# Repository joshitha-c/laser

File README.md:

# ESP32-C3 Laser Tripwire alarm

An intelligent, multi-layered laser security perimeter system built on the ESP32-C3 microcontroller. Features optical tripwire detection, case tamper sensing, motion tracking, real-time clock timestamps, and an OLED status display interface.

---

## Features

* **Triple-Layer Intrusion Detection:**
  * **Laser Tripwire:** Hardware-interrupt beam monitoring via photodiode and LM393 comparator.
  * **Case Tamper:** Microswitch detection if the enclosure lid is opened.
  * **Motion / Shake Guard:** 3-axis LIS3DH accelerometer monitoring for unit displacement or physical sabotage.
* **Visual & Audible Alerts:** 
  * SSD1306 128x64 OLED display showing live state, system time (DS1307 RTC), battery percentage, and specific trip causes.
  * Transistor-driven 3.3V active buzzer siren.
* **Simulation Ready:** Pre-configured for seamless compilation in PlatformIO and testing in the Wokwi simulator.

---

## Hardware Pinout Mapping

| ESP32-C3 Pin | Component / Connection | Type / Logic |
| :--- | :--- | :--- |
| **`GPIO0`** | Photodiode Level | Analog Input |
| **`GPIO1`** | LM393 Laser Trip Signal | Digital Input (Active LOW) |
| **`GPIO2`** | I2C Data (`SDA`) | OLED Display, DS1307 RTC, LIS3DH |
| **`GPIO3`** | I2C Clock (`SCL`) | OLED Display, DS1307 RTC, LIS3DH |
| **`GPIO4`** | Siren Buzzer Driver (`Q1`) | Digital Output (PWM/Pulse) |
| **`GPIO5`** | Arm / Disarm Pushbutton | Digital Input (Active HIGH) |
| **`GPIO6`** | LIS3DH Motion Interrupt (`INT1`) | Digital Input |
| **`GPIO7`** | Battery Sense (100kΩ / 100kΩ Divider) | Analog Input |
| **`GPIO10`**| Case Tamper Microswitch | Digital Input (Active HIGH) |

---
## How to Open and Use the ZIP Project in VS Code

Follow these steps to extract, open, and run the project inside Visual Studio Code using PlatformIO and the Wokwi Simulator.
The zip file:it is in repo releases.
### 1. Unzip the Project Folder
1. Locate the downloaded `.zip` file on your computer.
2. Right-click the `.zip` file and select **Extract All...** (Windows) or double-click it (macOS).
3. Choose a destination directory (e.g., your Desktop or Projects folder) and finish the extraction.

---

### 2. Install Required Extensions in VS Code
If you haven't set up Visual Studio Code for ESP32 development yet, install the required tools:

1. Open **Visual Studio Code**.
2. Click on the **Extensions** icon on the left sidebar (or press `Ctrl + Shift + X`).
3. Search for and install the following two extensions:
   * **[PlatformIO IDE](https://marketplace.visualstudio.com/items?itemName=platformio.platformio-ide)** (Handles building and compiling C++ code for ESP32)
   * **[Wokwi Simulator](https://marketplace.visualstudio.com/items?itemName=Wokwi.wokwi-vscode)** (Simulates the ESP32 hardware and screen)

---

### 3. Open the Extracted Project
1. In VS Code, go to **File** $\rightarrow$ **Open Folder...** (or press `Ctrl + K, Ctrl + O`).
2. Navigate to the folder you extracted in **Step 1**.
3. Select the root folder (the folder containing `platformio.ini` and `wokwi.toml`) and click **Select Folder**.
4. If prompted with *"Do you trust the authors of the files in this folder?"*, click **Yes, I trust the authors**.

---

### 4. Build and Run the Project

#### Option A: Running in Wokwi Simulator (Virtual Hardware)
1. Open the **`diagram.json`** file from the left Explorer pane.
2. Press `Ctrl + Shift + P` (or `Cmd + Shift + P` on Mac) to open the VS Code Command Palette.
3. Type **`Wokwi: Start Simulator`** and press **Enter**.
4. The simulation window will open directly in VS Code, displaying the ILI9341 screen and animated buttons.

# Buzzer audio in vs Code:
* The buzzer noise when running the Wokwi simulator inside the VS Code . The vscode mutes the sounfd from the wokwi simulator so you can't hear it. 
* If you want to listen to the sound effects and music, open the diagram.json file online directly at **[Wokwi.com](https://wokwi.com)**.

---

#  Battery Level Simulation (Potentiometer Knob):
*  In the simulator, the battery level is simulated using a potentiometer (rotary knob).
* How to test battery levels: While the simulation is running, click and drag the knob clockwise on the potentiometer in the simulator window to increase or decrease the voltage.
## schematics:

## pcb:

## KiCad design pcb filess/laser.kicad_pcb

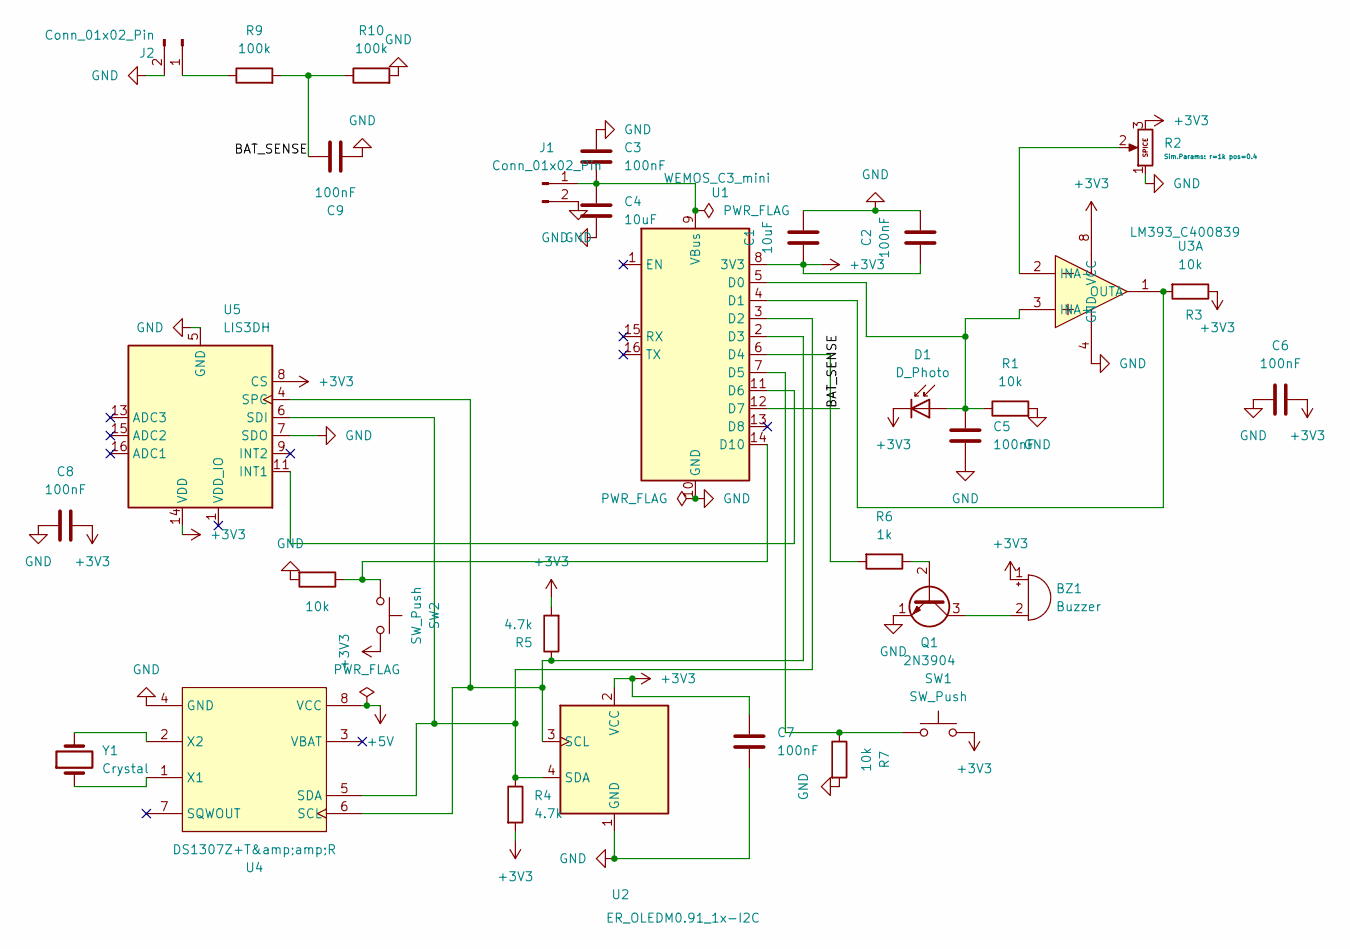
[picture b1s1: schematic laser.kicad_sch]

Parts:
BZ1: Buzzer; Buzzer_12x9.5RM7.6
C1, C4: 10uF; C_0805_2012Metric
C2, C3, C5, C6, C7, C8, C9: 100nF; C_0805_2012Metric
D1: D_Photo; LED_1206_3216Metric
J1: Conn_01x02_Pin; PinHeader_1x02_P2.54mm_Vertical
J2: Conn_01x02_Pin; JST_PH_B2B-PH-K_1x02_P2.00mm_Vertical
Q1: 2N3904; TO-92_Inline
R1, R3, R7, R8: 10k; R_0805_2012Metric
R2: Potentiometer; Potentiometer_Bourns_3296W_Vertical
R4, R5: 4.7k; R_0805_2012Metric
R6: 1k; R_0805_2012Metric
R9, R10: 100k; R_0805_2012Metric
SW1, SW2: SW_Push; SW_SPST_TL3342
U1: WEMOS_C3_mini
U2: ER_OLEDM0.91_1x-I2C
U3: LM393_C400839; SOP-8_L4.9-W3.9-P1.27-LS6.0-BL; MPN LM393; LCSC Part C400839
U4: DS1307Z+T&amp;amp;R; SOIC-8_L5.0-W4.0-P1.27-LS6.0-BL; MPN DS1307Z+T&R; LCSC Part C9868
U5: LIS3DH; LGA-16_3x3mm_P0.5mm_LayoutBorder3x5y
Y1: Crystal; Crystal_AT310_D3.0mm_L10.0mm_Horizontal

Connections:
+3V3: BZ1.1 (+), C1.1, C2.1, C6.2, C7.2, C8.2, D1.1 (K), R2.3, R3.1, R4.2, R5.2, SW1.2, SW2.2, U1.8 (3V3), U2.2 (VCC), U3.8 (VCC), U5.8 (CS), U5.14 (VDD)
+5V: U4.8 (VCC)
/BAT_SENSE: C9.2, R9.2, R10.1, U1.12 (D7)
GND: C1.2, C2.2, C3.1, C4.2, C5.2, C6.1, C7.1, C8.1, C9.1, J1.2, J2.2, Q1.1 (E), R1.2, R2.1, R7.2, R8.2, R10.2, U1.10 (GND), U2.1 (GND), U3.4 (GND), U4.4 (GND), U5.5 (GND), U5.7 (SDO), U5.10 (GND), U5.12 (GND)
unnamed: BZ1.2 (-), Q1.3 (C)
unnamed: C5.1, D1.2 (A), R1.1, U1.5 (D0), U3.3 (INA+)
unnamed: C3.2, C4.1, J1.1, U1.9 (VBus)
unnamed: J2.1, R9.1
unnamed: Q1.2 (B), R6.1
unnamed: R3.2, U1.4 (D1), U3.1 (OUTA)
unnamed: R4.1, U1.3 (D2), U2.4 (SDA), U4.5 (SDA), U5.6 (SDI)
unnamed: R5.1, U1.2 (D3), U2.3 (SCL), U4.6 (SCL), U5.4 (SPC)
unnamed: R6.2, U1.6 (D4)
unnamed: R7.1, SW1.1, U1.7 (D5)
unnamed: U1.11 (D6), U5.11 (INT1)
unnamed: R8.1, SW2.1, U1.14 (D10)
unnamed: R2.2, U3.2 (INA-)
unnamed: U4.1 (X1), Y1.1
unnamed: U4.2 (X2), Y1.2

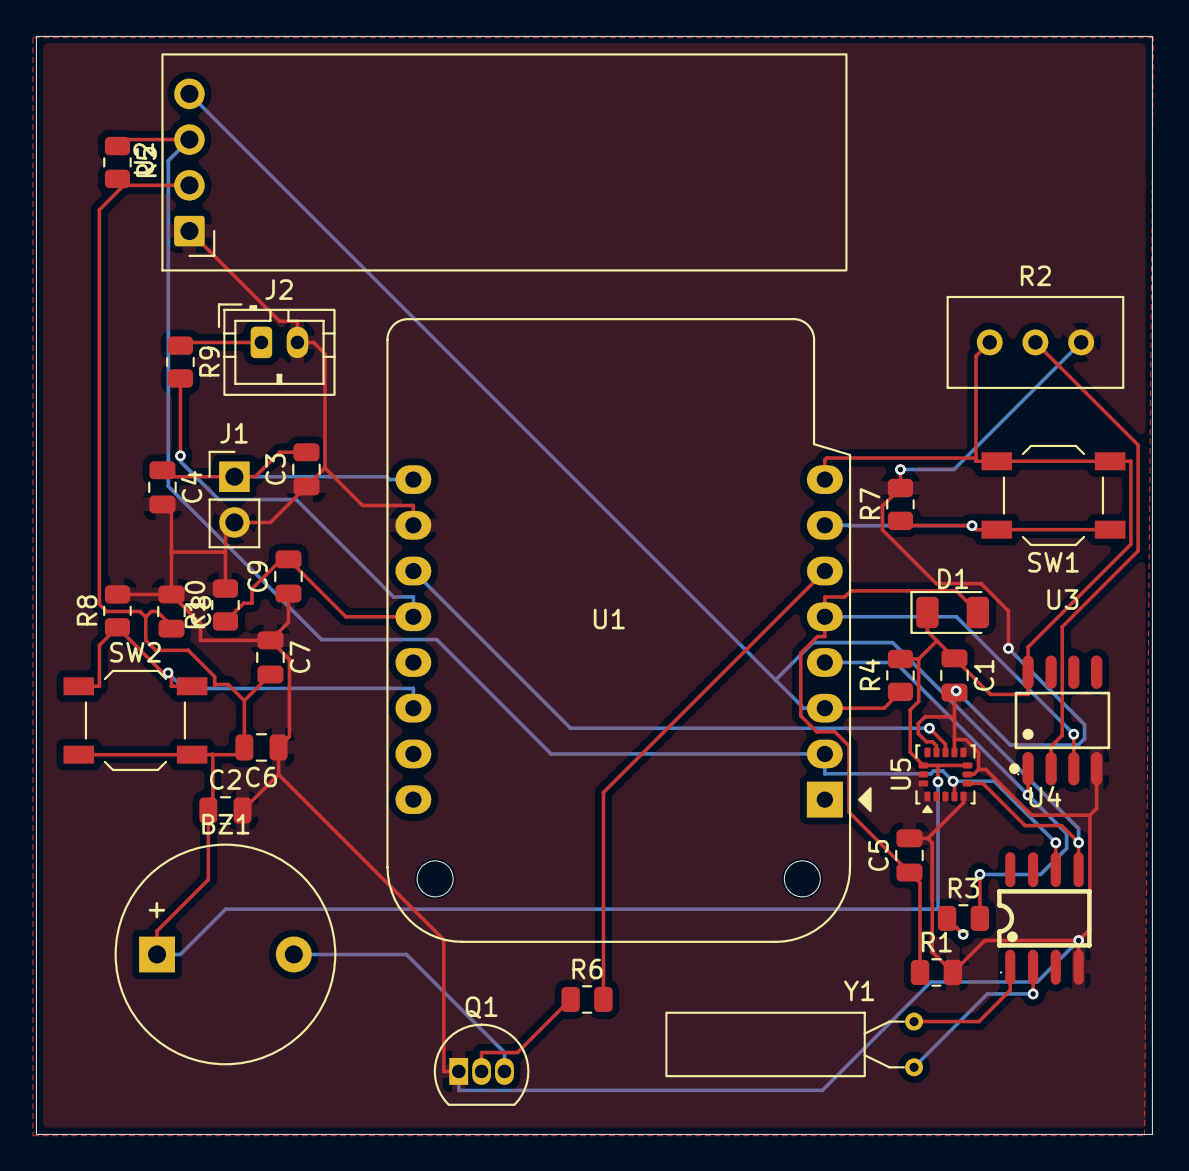
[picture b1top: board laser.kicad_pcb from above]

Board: 2 copper layers, 62.0 x 61.0 mm, 32 parts (0 on the bottom side), 18 nets.
